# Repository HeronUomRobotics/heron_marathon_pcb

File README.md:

# heron_marathon_pcb
A Repository of Heron UoM Robotics Chapter of IEEE, specific for design PCB

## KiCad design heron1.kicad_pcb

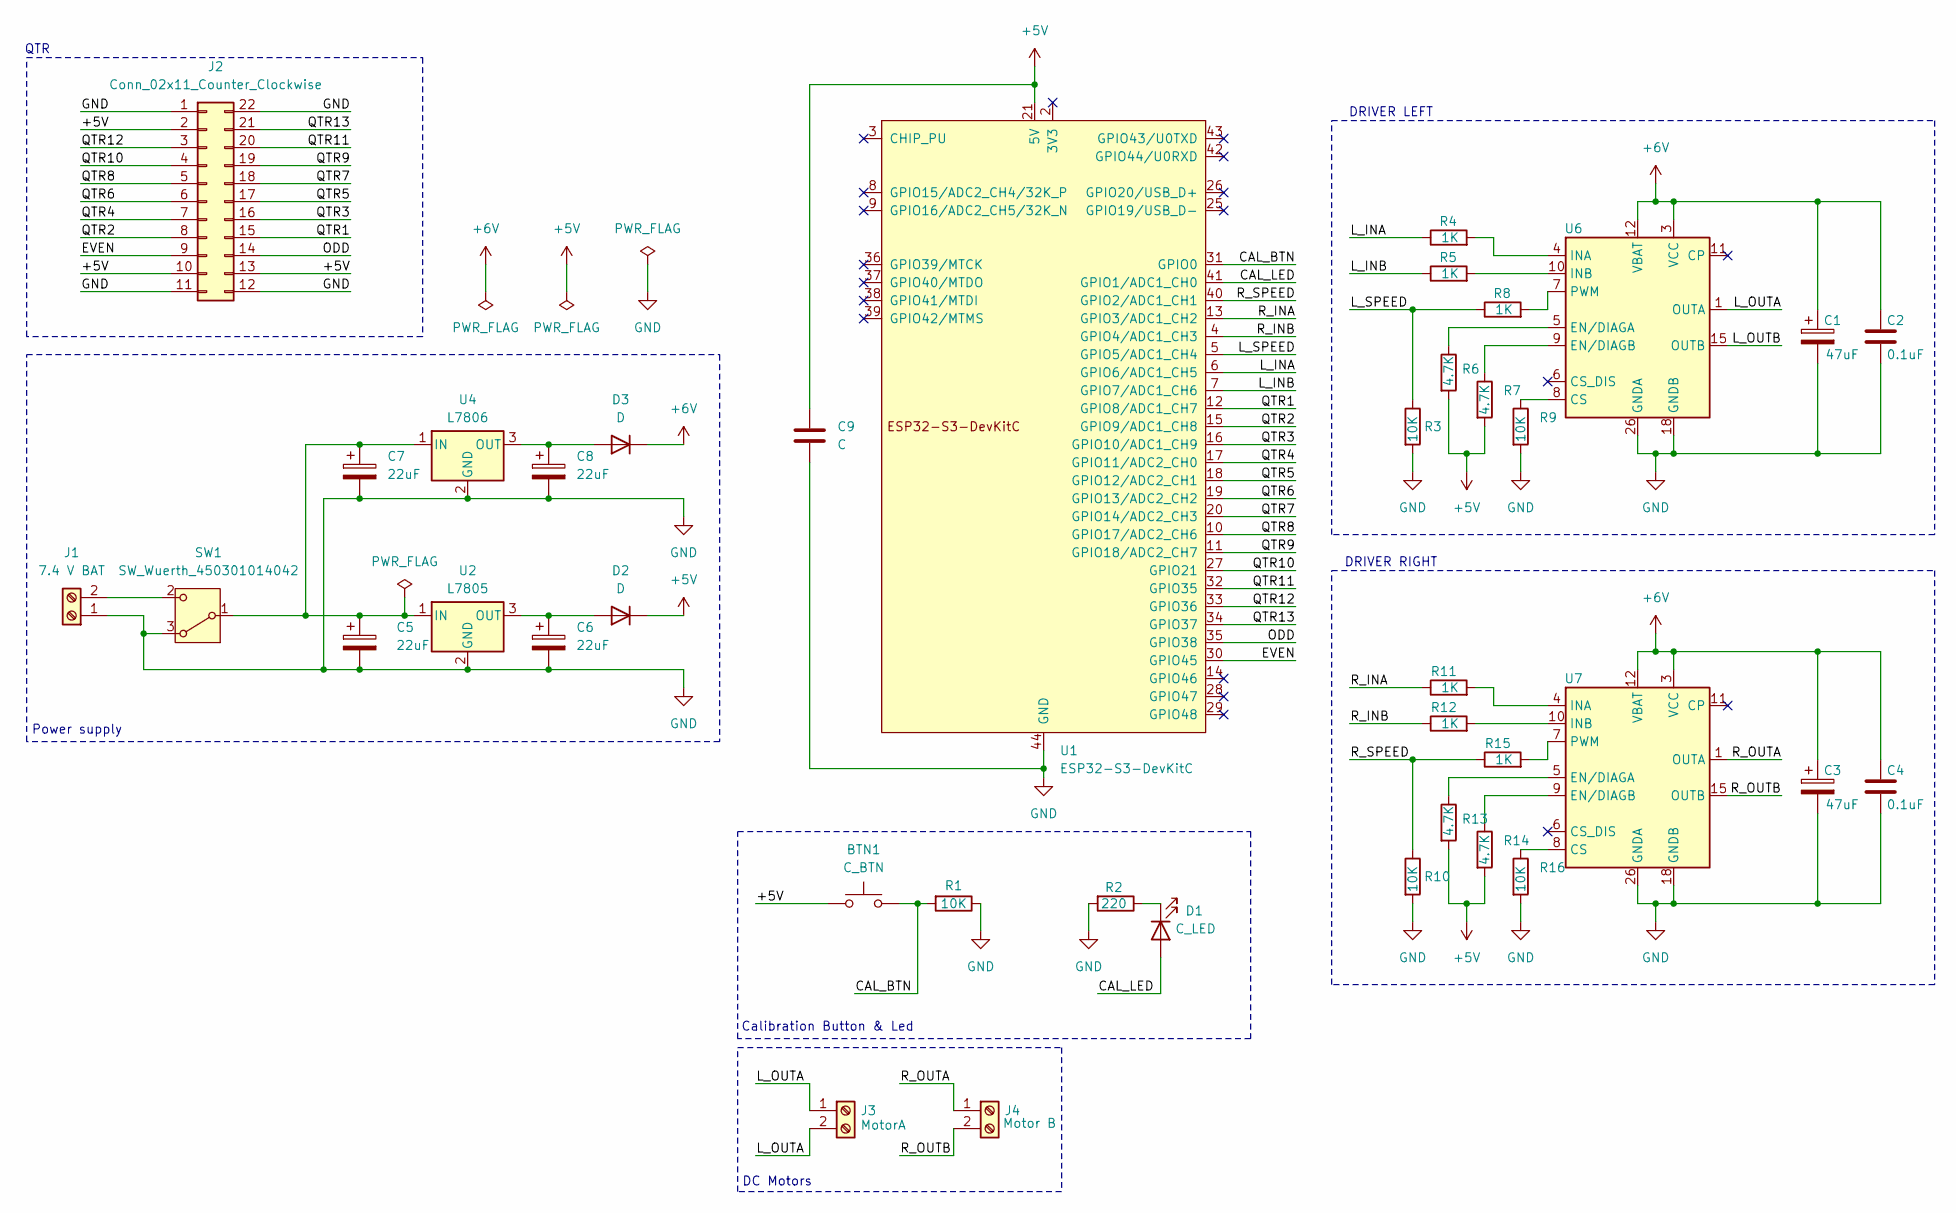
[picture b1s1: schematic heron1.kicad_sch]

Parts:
BTN1: C_BTN; SW_SPST_PTS645
C1, C3: 47uF; CP_Radial_D5.0mm_P2.50mm
C2, C4: 0.1uF; C_0603_1608Metric
C5, C6, C7, C8: 22uF; CP_Radial_D5.0mm_P2.50mm
C9: C; C_0805_2012Metric
D1: C_LED; LED_0805_2012Metric
D2, D3: D; D_1206_3216Metric
J1: 7.4 V BAT; TerminalBlock_Phoenix_MPT-0,5-2-2.54_1x02_P2.54mm_Horizontal
J2: Conn_02x11_Counter_Clockwise; TE_2-84952-2_1x22-1MP_P1.0mm_Horizontal
J3: MotorA; TerminalBlock_Phoenix_MPT-0,5-2-2.54_1x02_P2.54mm_Horizontal
J4: Motor B; TerminalBlock_Phoenix_MPT-0,5-2-2.54_1x02_P2.54mm_Horizontal
R1, R3, R9, R10, R16: 10K; R_1206_3216Metric
R2: 220; R_0603_1608Metric
R4, R5, R8, R11, R12, R15: 1K; R_0402_1005Metric
R6, R7, R13, R14: 4.7K; R_0805_2012Metric
SW1: SW_Wuerth_450301014042; SW_Slide-03_Wuerth-WS-SLTV_10x2.5x6.4_P2.54mm
U1: ESP32-S3-DevKitC
U2: L7805; TO-252-2
U4: L7806; TO-252-2
U6, U7: VNH5019A-E; ST_MultiPowerSO-30

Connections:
+5V: BTN1.1, C9.1, D2.1 (K), J2.2, J2.10, J2.13, R6.2, R7.2, R13.2, R14.2, U1.21 (5V)
+6V: C1.1, C2.1, C3.1, C4.1, D3.1 (K), U6.3 (VCC), U6.12 (VBAT), U6.13 (VCC), U6.23 (VCC), U6.31 (VCC), U7.3 (VCC), U7.12 (VBAT), U7.13 (VCC), U7.23 (VCC), U7.31 (VCC)
/CAL_BTN: BTN1.2, R1.2, U1.31 (GPIO0)
/CAL_LED: D1.2 (A), U1.41 (GPIO1/ADC1_CH0)
/EVEN: J2.9, U1.30 (GPIO45)
/L_INA: R4.1, U1.6 (GPIO6/ADC1_CH5)
/L_INB: R5.1, U1.7 (GPIO7/ADC1_CH6)
/L_OUTA: J3.1, J3.2, U6.1 (OUTA), U6.25 (OUTA), U6.30 (OUTA), U6.33 (OUTA)
/L_OUTB: U6.15 (OUTB), U6.16 (OUTB), U6.21 (OUTB), U6.32 (OUTB)
/L_SPEED: R3.1, R8.1, U1.5 (GPIO5/ADC1_CH4)
/ODD: J2.14, U1.35 (GPIO38)
/QTR1: J2.15, U1.12 (GPIO8/ADC1_CH7)
/QTR2: J2.8, U1.15 (GPIO9/ADC1_CH8)
/QTR3: J2.16, U1.16 (GPIO10/ADC1_CH9)
/QTR4: J2.7, U1.17 (GPIO11/ADC2_CH0)
/QTR5: J2.17, U1.18 (GPIO12/ADC2_CH1)
/QTR6: J2.6, U1.19 (GPIO13/ADC2_CH2)
/QTR7: J2.18, U1.20 (GPIO14/ADC2_CH3)
/QTR8: J2.5, U1.10 (GPIO17/ADC2_CH6)
/QTR9: J2.19, U1.11 (GPIO18/ADC2_CH7)
/QTR10: J2.4, U1.27 (GPIO21)
/QTR11: J2.20, U1.32 (GPIO35)
/QTR12: J2.3, U1.33 (GPIO36)
/QTR13: J2.21, U1.34 (GPIO37)
/R_INA: R11.1, U1.13 (GPIO3/ADC1_CH2)
/R_INB: R12.1, U1.4 (GPIO4/ADC1_CH3)
/R_OUTA: J4.1, U7.1 (OUTA), U7.25 (OUTA), U7.30 (OUTA), U7.33 (OUTA)
/R_OUTB: J4.2, U7.15 (OUTB), U7.16 (OUTB), U7.21 (OUTB), U7.32 (OUTB)
/R_SPEED: R10.1, R15.1, U1.40 (GPIO2/ADC1_CH1)
GND: C1.2, C2.2, C3.2, C4.2, C5.2, C6.2, C7.2, C8.2, C9.2, J1.1, J2.1, J2.11, J2.12, J2.22, R1.1, R2.2, R3.2, R9.2, R10.2, R16.2, SW1.3 (A), U1.22 (GND), U1.23 (GND), U1.24 (GND), U1.44 (GND), U2.2 (GND), U4.2 (GND), U6.18 (GNDB), U6.19 (GNDB), U6.20 (GNDB), U6.26 (GNDA), U6.27 (GNDA), U6.28 (GNDA), U7.18 (GNDB), U7.19 (GNDB), U7.20 (GNDB), U7.26 (GNDA), U7.27 (GNDA), U7.28 (GNDA)
unnamed: D1.1 (K), R2.1
unnamed: C6.1, D2.2 (A), U2.3 (OUT)
unnamed: C8.1, D3.2 (A), U4.3 (OUT)
unnamed: J1.2, SW1.2 (C)
unnamed: C5.1, C7.1, SW1.1 (B), U2.1 (IN), U4.1 (IN)
unnamed: R9.1, U6.8 (CS)
unnamed: R6.1, U6.5 (EN/DIAGA)
unnamed: R7.1, U6.9 (EN/DIAGB)
unnamed: R4.2, U6.4 (INA)
unnamed: R5.2, U6.10 (INB)
unnamed: R8.2, U6.7 (PWM)
unnamed: R16.1, U7.8 (CS)
unnamed: R13.1, U7.5 (EN/DIAGA)
unnamed: R14.1, U7.9 (EN/DIAGB)
unnamed: R11.2, U7.4 (INA)
unnamed: R12.2, U7.10 (INB)
unnamed: R15.2, U7.7 (PWM)

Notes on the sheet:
Power supply
QTR
DRIVER LEFT
DC Motors
DRIVER RIGHT
Calibration Button & Led

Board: 2 copper layers, 39 parts (0 on the bottom side), 47 nets, no tracks yet.

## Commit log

2024-12-13 Initial Commit First Attempt to build a pcb marathon competitive car
2025-01-10 added new drivers
2025-01-10 added arduino nano 33 iot
2025-01-12 started connecting new drivers
2025-01-27 latest
2025-02-04 custom drivers created
2025-02-05 Updated version of pcb to use esp32 s3 devkitc-1
2025-02-05 Updated PCB layout
2025-02-05 first stage pcb
